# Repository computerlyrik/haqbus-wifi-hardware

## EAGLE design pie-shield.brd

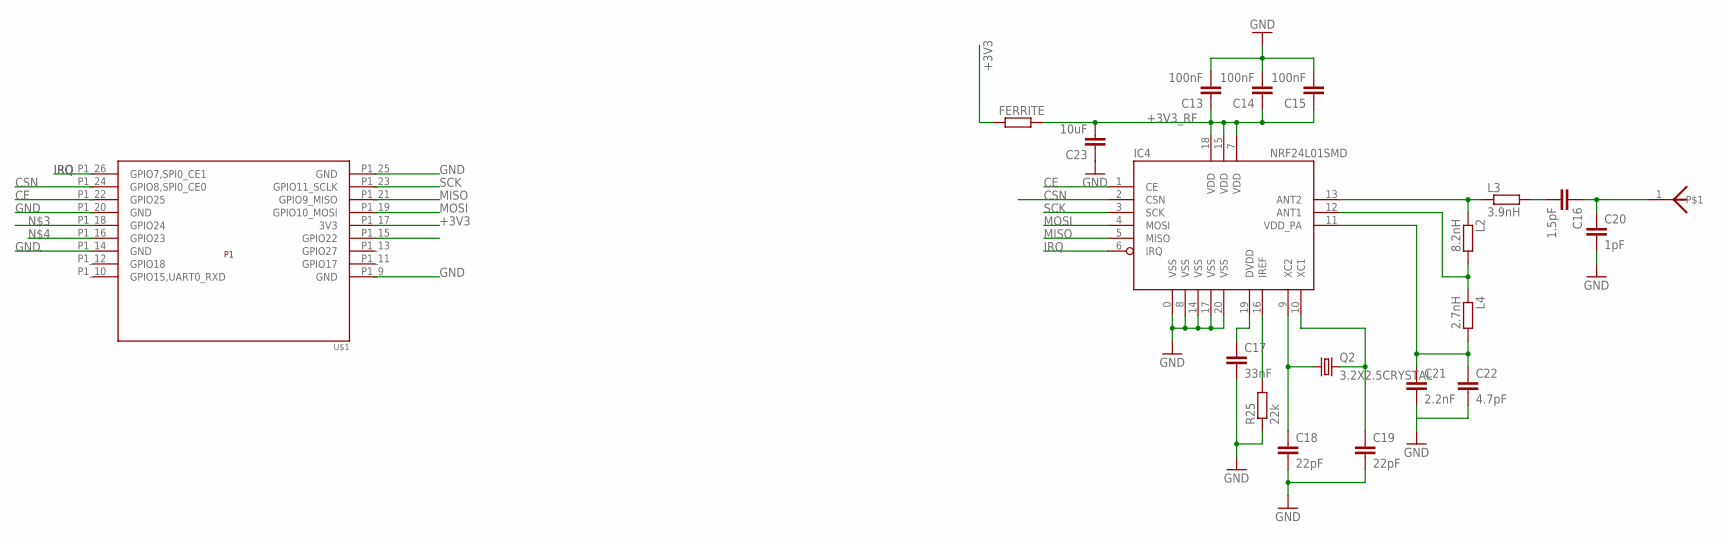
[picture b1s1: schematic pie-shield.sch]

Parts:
ANT: CHIPANTENNA
C13, C14, C15: 100nF; C0402K
C16: 1.5pF; C0402K
C17: 33nF; C0402K
C18, C19: 22pF; C0402K
C20: 1pF; C0402K
C21: 2.2nF; C0402K
C22: 4.7pF; C0402K
C23: 10uF; C0805K
FERRITE: R-EU_R0805; R0805
IC4: NRF24L01SMD; QFN20
L2: 8.2nH; R0402
L3: 3.9nH; R0402
L4: 2.7nH; R0402
Q2: 3.2X2.5CRYSTAL; CRYSTAL3.2X2.5
R25: 22k; R0603
U$1: RASPBERRY-PI_REV2

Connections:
+3V3: FERRITE.1, U$1.P1_17 (3V3)
+3V3_RF: C13.1, C14.1, C15.1, C23.2, FERRITE.2, IC4.7 (VDD), IC4.15 (VDD), IC4.18 (VDD)
CE: IC4.1 (CE), U$1.P1_22 (GPIO25)
CSN: IC4.2 (CSN), U$1.P1_24 (GPIO8,SPI0_CE0)
GND: C13.2, C14.2, C15.2, C17.2, C18.2, C19.2, C20.2, C21.2, C22.2, C23.1, IC4.0 (VSS), IC4.8 (VSS), IC4.14 (VSS), IC4.17 (VSS), IC4.20 (VSS), R25.1, U$1.P1_9 (GND), U$1.P1_14 (GND), U$1.P1_20 (GND), U$1.P1_25 (GND)
IRQ: IC4.6 (IRQ), U$1.P1_26 (GPIO7,SPI0_CE1)
MISO: IC4.5 (MISO), U$1.P1_21 (GPIO9_MISO)
MOSI: IC4.4 (MOSI), U$1.P1_19 (GPIO10_MOSI)
unnamed: C18.1, IC4.9 (XC2), Q2.1
unnamed: C19.1, IC4.10 (XC1), Q2.3 (2)
unnamed: ANT.1, C16.1, C20.1
unnamed: C17.1, IC4.19 (DVDD)
unnamed: IC4.16 (IREF), R25.2
unnamed: C21.1, C22.1, IC4.11 (VDD_PA), L4.2
unnamed: IC4.12 (ANT1), L2.2, L4.1
unnamed: IC4.13 (ANT2), L2.1, L3.1
unnamed: C16.2, L3.2
SCK: IC4.3 (SCK), U$1.P1_23 (GPIO11_SCLK)

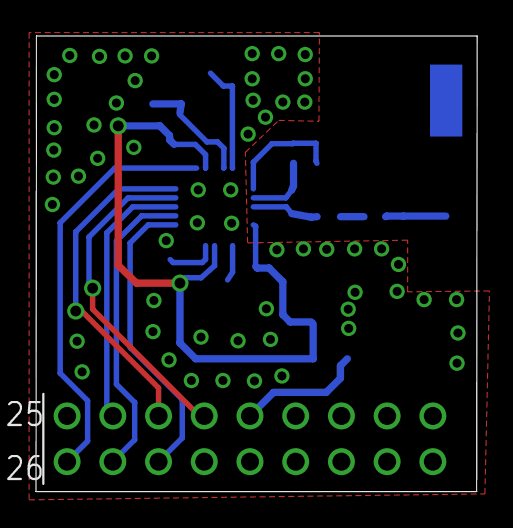
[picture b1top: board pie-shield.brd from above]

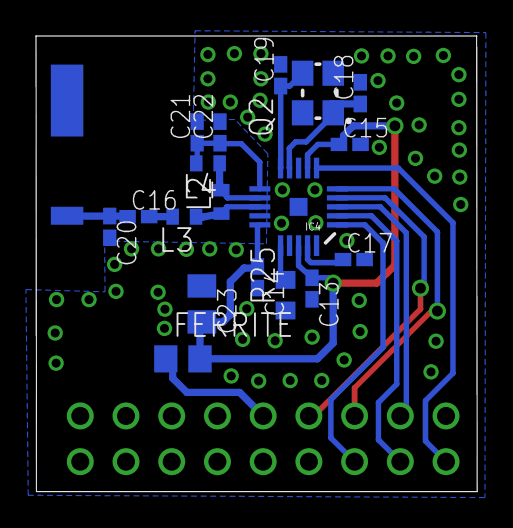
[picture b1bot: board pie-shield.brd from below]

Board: 2 copper layers, 24.5 x 25.3 mm, 20 parts (19 on the bottom side), 18 nets.

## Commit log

2013-01-20 initial commit of beta 0.1
2013-01-20 sized board down
2013-01-20 minisized
2013-01-20 wired board
2013-01-20 more space for antenna
2013-01-20 minified and dru tested
2013-01-21 1 square inch reached
2013-01-21 fixed layout mirrored it
2013-01-21 updated to smaller version of raspberry io
2013-01-21 fixed drill holes - removed
